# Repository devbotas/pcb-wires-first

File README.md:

# The Problem

Wireless IoT sucks.

It's unreliable and breaks all the time. There's not such thing as reliable, maintenance-free, wireless IoT.

If it runs on batteries - that's even worse.

Another problem - central IoT hubs. If those break, lose connection, decides to reboot ar whatever - my smart house immediatelly becomes non-functional.

# The Solution

Put the analog wires first! So that light switches continue to operate even if smart features decide to stop working.

# The Boards

## Gateway

This is a simple carrier board for WizNET W55RP20 development module. It cannot do much by itself - maybe blink some LEDs. Real functionality (and also power) should come from the JST PH headers.

Can be mounted on M or L size Holey board.

## Voltage converter

Takes 12-24V input (technically, 5-70V, but these voltages may not be supported on the other modules that this one is supposed to power) and creates 3.3V output so Gateway or other low power modules could be connected through the JST XH connector. Additionally, there are multiple JST VH connectors, which act as a power switch to connect multiple power hungry modules, like the Switcher.

Two can be mounted on a single Holey-S board.

## Switcher

Originally meant to control LED lights, but it can switch anything. It has one switchable 12/24V output (should be able to handle 4A). Output can be controlled simultaneously in multiple ways:

* ON wire: shorting this to GND for 100ms will turn the switch on.
* OFF wire: shorting this to GND for 100ms will turn the switch off.
* TGL wire: shorting this to GND for 100ms will toggle the switch.
* I2C directly: software based commands that can turn switch on or off and read the current state.

The idea here that ON/OFF/TGL signals could be wired to the physical wall switches directly, any smart features being entirely optional. So the switch will operate as a dumb-switch.

Renesas HVPAK SLG47115 chip serves both as a high-power switch and an input sanitizer. For example, if faulty hardware shorts ON signal to GND permanently, OFF and TGL signals continue to operate normally. 

Two can be mounted on a single Holey-S board.

## Holey boards

These are very handy to mount modules listed above, or maybe anything. They have a grid of 3.2mm diameter holes (hence the name) on a 5mm grid. They work perfectly with any M3 mounting hardware and come in the following sizes:

* L - 160x100 mm
* M - 100x80 mm
* S - 80x40 mm

So, one M board can fit exactly two S boards, and one L board can fit exactly 2 M boards. This allows some neat and functional arrangement.

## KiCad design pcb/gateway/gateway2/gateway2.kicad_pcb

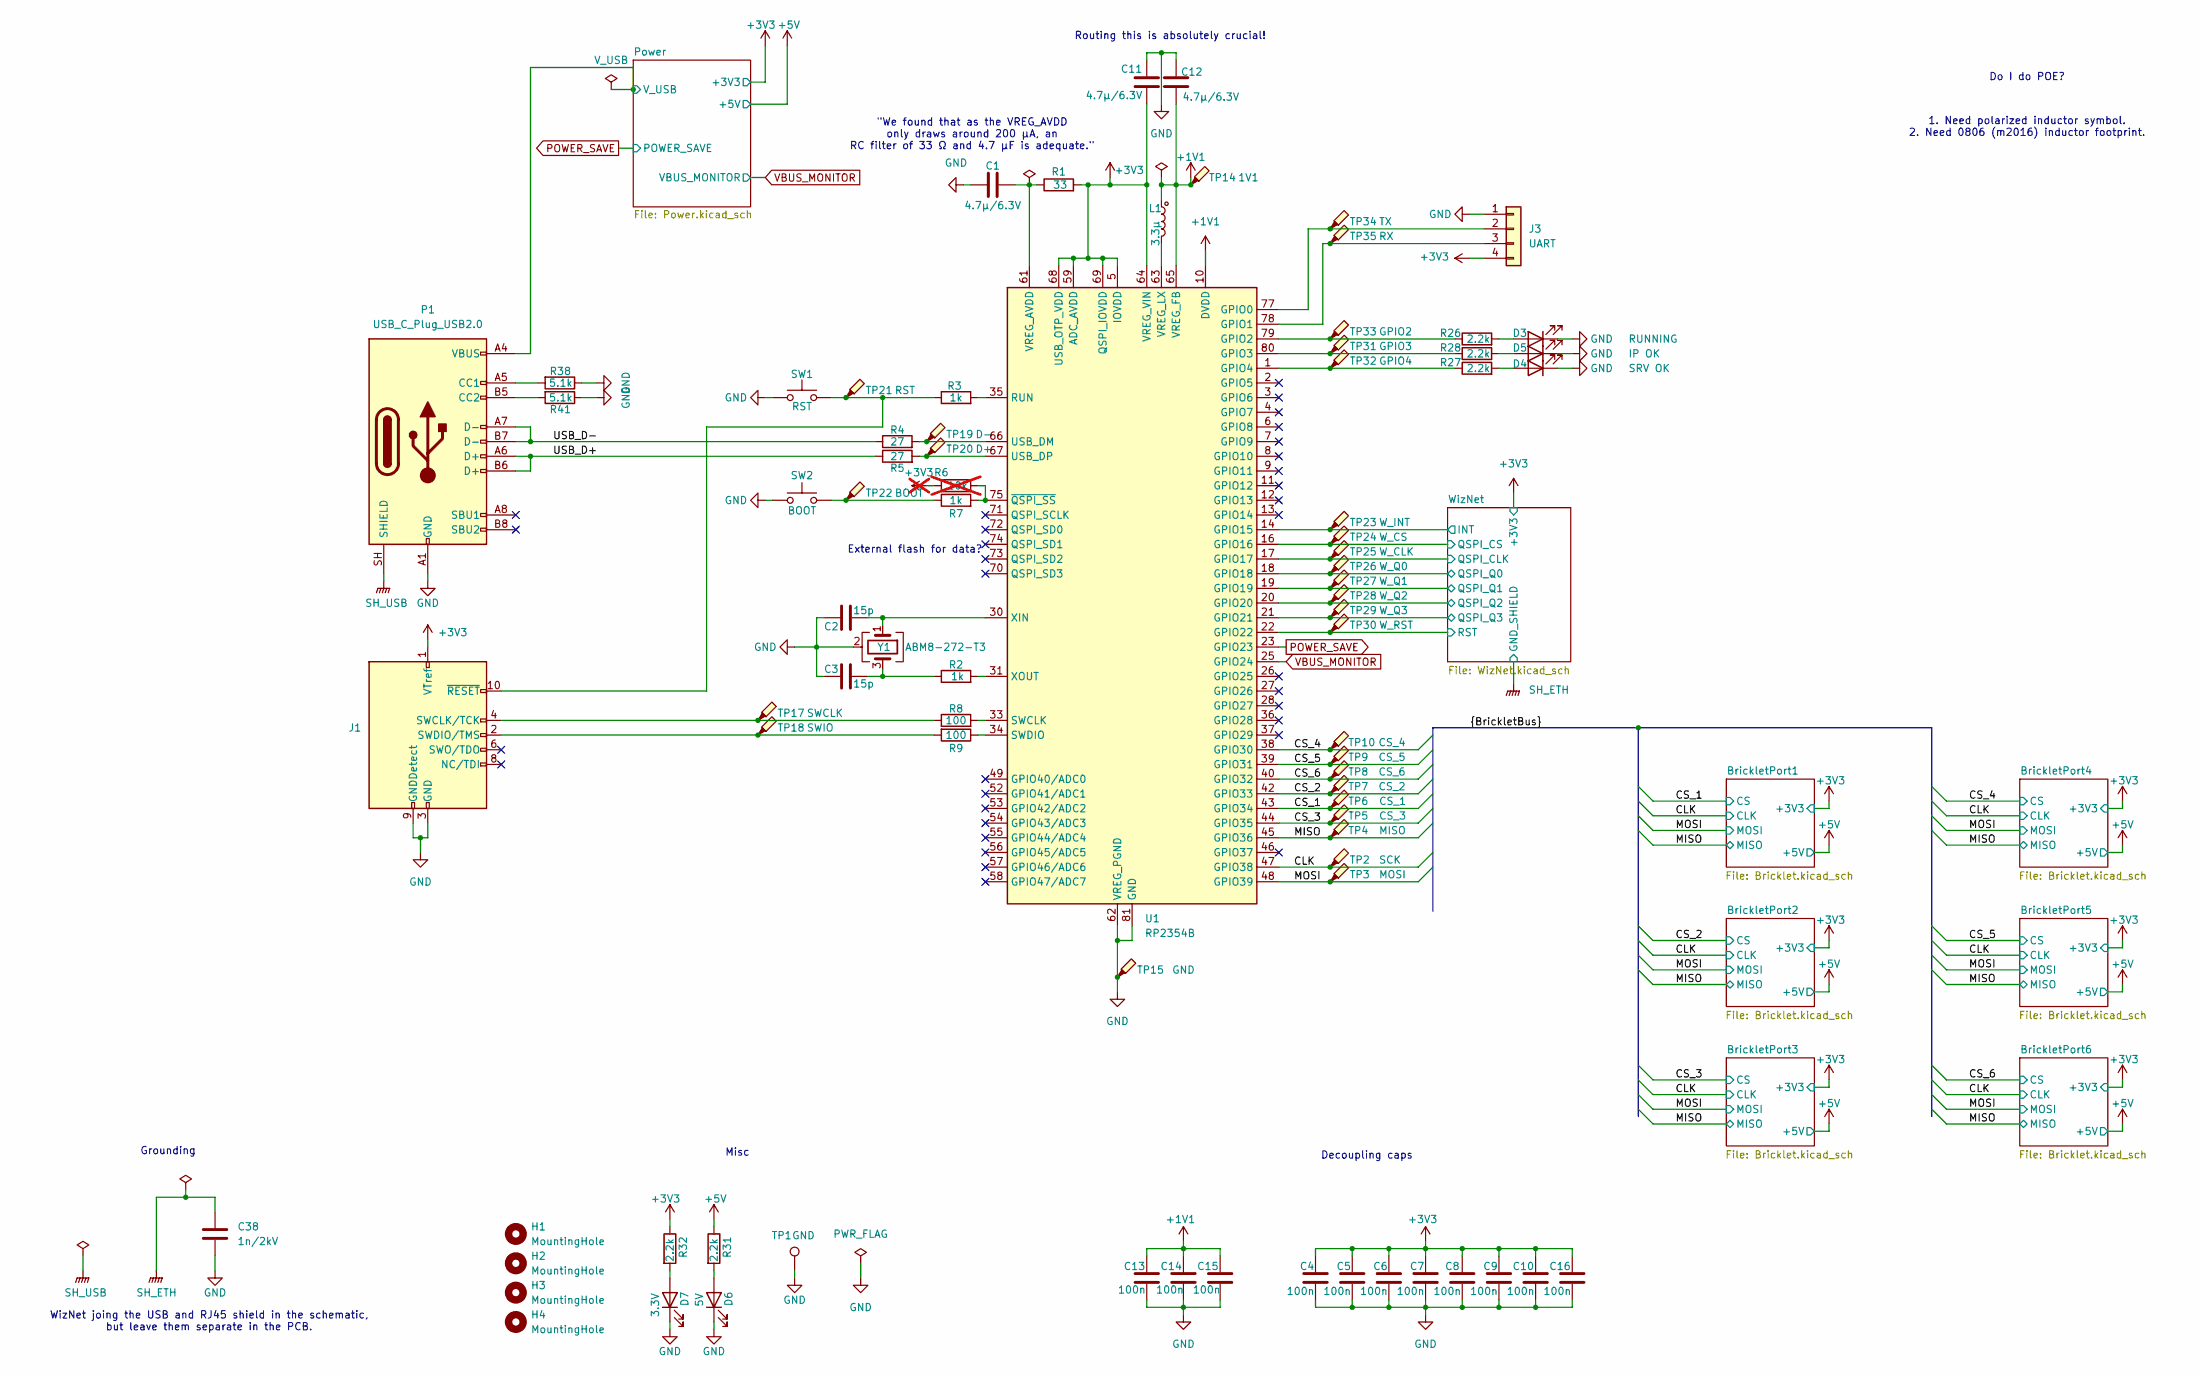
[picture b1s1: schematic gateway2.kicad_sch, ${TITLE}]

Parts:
C1, C11, C12: 4.7μ/6.3V; C_0603_1608Metric
C2, C3: 15p; C_0603_1608Metric
C4, C5, C6, C7, C8, C9, C10, C13, C14, C15, C16: 100n; C_0603_1608Metric
C38: 1n/2kV; C_0603_1608Metric
D3: RUNNING; D_0603_1608Metric
D4: SRV OK; D_0603_1608Metric
D5: IP OK; D_0603_1608Metric
D6: 5V; D_0603_1608Metric
D7: 3.3V; D_0603_1608Metric
H1, H2, H3, H4: MountingHole; MountingHole_3.2mm_M3_NoCopper
J1: Conn_ARM_JTAG_SWD_10; PinHeader_2x05_P1.27mm_Vertical_SMD
J3: UART; JST_PH_B4B-PH-K_1x04_P2.00mm_Vertical
L1: 3.3µ; L_Abracon_AOTA-B201610S
P1: USB_C_Plug_USB2.0; USB_C_Receptacle_GCT_USB4085
R1: 33; R_0603_1608Metric
R2, R3, R7: 1k; R_0603_1608Metric
R4, R5: 27; R_0603_1608Metric
R6: 10k; R_0603_1608Metric; not fitted
R8, R9: 100; R_0603_1608Metric
R26, R27, R28, R31, R32: 2.2k; R_0603_1608Metric
R38, R41: 5.1k; R_0603_1608Metric
SW1: RST; SW_SPST_CK_PTS815_Sx250SMTR_LFS
SW2: BOOT; SW_SPST_CK_PTS815_Sx250SMTR_LFS
TP1: GND; TestPoint_Keystone_5019_Miniature
TP2: SCK; TestPoint_Pad_D1.0mm
TP3: MOSI; TestPoint_Pad_D1.0mm
TP4: MISO; TestPoint_Pad_D1.0mm
TP5: CS_3; TestPoint_Pad_D1.0mm
TP6: CS_1; TestPoint_Pad_D1.0mm
TP7: CS_2; TestPoint_Pad_D1.0mm
TP8: CS_6; TestPoint_Pad_D1.0mm
TP9: CS_5; TestPoint_Pad_D1.0mm
TP10: CS_4; TestPoint_Pad_D1.0mm
TP14: 1V1; TestPoint_Pad_D1.0mm
TP15: GND; TestPoint_Pad_D1.0mm
TP17: SWCLK; TestPoint_Pad_D1.0mm
TP18: SWIO; TestPoint_Pad_D1.0mm
TP19: D-; TestPoint_Pad_D1.0mm
TP20: D+; TestPoint_Pad_D1.0mm
TP21: RST; TestPoint_Pad_D1.0mm
TP22: BOOT; TestPoint_Pad_D1.0mm
TP23: W_INT; TestPoint_Pad_D1.0mm
TP24: W_CS; TestPoint_Pad_D1.0mm
TP25: W_CLK; TestPoint_Pad_D1.0mm
TP26: W_Q0; TestPoint_Pad_D1.0mm
TP27: W_Q1; TestPoint_Pad_D1.0mm
TP28: W_Q2; TestPoint_Pad_D1.0mm
TP29: W_Q3; TestPoint_Pad_D1.0mm
TP30: W_RST; TestPoint_Pad_D1.0mm
TP31: GPIO3; TestPoint_Pad_D1.0mm
TP32: GPIO4; TestPoint_Pad_D1.0mm
TP33: GPIO2; TestPoint_Pad_D1.0mm
TP34: TX; TestPoint_Pad_D1.0mm
TP35: RX; TestPoint_Pad_D1.0mm
U1: RP2354B; QFN-80-1EP_10x10mm_P0.4mm_EP3.4x3.4mm
Y1: ABM8-272-T3; Crystal_SMD_Abracon_ABM8G-4Pin_3.2x2.5mm

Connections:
+1V1: C12.1, C13.2, C14.2, C15.2, L1.1, TP14.1 (1_1), U1.10 (DVDD), U1.32 (DVDD), U1.51 (DVDD), U1.65 (VREG_FB)
+3V3: C4.2, C5.2, C6.2, C7.2, C8.2, C9.2, C10.2, C11.1, C16.2, J1.1 (VTref), J3.4, R1.2, R6.1, R32.1, U1.5 (IOVDD), U1.15 (IOVDD), U1.24 (IOVDD), U1.29 (IOVDD), U1.41 (IOVDD), U1.50 (IOVDD), U1.59 (ADC_AVDD), U1.60 (IOVDD), U1.64 (VREG_VIN), U1.68 (USB_OTP_VDD), U1.69 (QSPI_IOVDD), U1.76 (IOVDD); also elsewhere on the board
+5V: R31.1; also elsewhere on the board
/CLK: TP2.1 (1_1), U1.47 (GPIO38); also elsewhere on the board
/CS_1: TP6.1 (1_1), U1.43 (GPIO34); also elsewhere on the board
/CS_2: TP7.1 (1_1), U1.42 (GPIO33); also elsewhere on the board
/CS_3: TP5.1 (1_1), U1.44 (GPIO35); also elsewhere on the board
/CS_4: TP10.1 (1_1), U1.38 (GPIO30); also elsewhere on the board
/CS_5: TP9.1 (1_1), U1.39 (GPIO31); also elsewhere on the board
/CS_6: TP8.1 (1_1), U1.40 (GPIO32); also elsewhere on the board
/MISO: TP4.1 (1_1), U1.45 (GPIO36); also elsewhere on the board
/MOSI: TP3.1 (1_1), U1.48 (GPIO39); also elsewhere on the board
/Power/V_USB: P1.A4 (VBUS), P1.A9 (VBUS), P1.B4 (VBUS), P1.B9 (VBUS); also elsewhere on the board
/USB_D+: P1.A6 (D+), P1.B6 (D+), R5.1
/USB_D-: P1.A7 (D-), P1.B7 (D-), R4.1
/WizNet/INT: TP23.1 (1_1), U1.14 (GPIO15); also elsewhere on the board
/WizNet/QSPI_CLK: TP25.1 (1_1), U1.17 (GPIO17); also elsewhere on the board
/WizNet/QSPI_CS: TP24.1 (1_1), U1.16 (GPIO16); also elsewhere on the board
/WizNet/QSPI_Q0: TP26.1 (1_1), U1.18 (GPIO18); also elsewhere on the board
/WizNet/QSPI_Q1: TP27.1 (1_1), U1.19 (GPIO19); also elsewhere on the board
/WizNet/QSPI_Q2: TP28.1 (1_1), U1.20 (GPIO20); also elsewhere on the board
/WizNet/QSPI_Q3: TP29.1 (1_1), U1.21 (GPIO21); also elsewhere on the board
/WizNet/RST: TP30.1 (1_1), U1.22 (GPIO22); also elsewhere on the board
GND: C1.1, C2.1, C3.1, C4.1, C5.1, C6.1, C7.1, C8.1, C9.1, C10.1, C11.2, C12.2, C13.1, C14.1, C15.1, C16.1, C38.1, D3.1 (K), D4.1 (K), D5.1 (K), D6.1 (K), D7.1 (K), J1.3 (GND), J1.5 (GND), J1.9 (GNDDetect), J3.1, P1.A1 (GND), P1.A12 (GND), P1.B1 (GND), P1.B12 (GND), R38.1, R41.1, SW1.1, SW2.1, TP1.1 (1_1), TP15.1 (1_1), U1.62 (VREG_PGND), U1.81 (GND), Y1.2 (G), Y1.4 (G); also elsewhere on the board
unnamed: C3.2, R2.1, Y1.3
unnamed: D3.2 (A), R26.2
unnamed: D4.2 (A), R27.2
unnamed: D5.2 (A), R28.2
unnamed: D6.2 (A), R31.2
unnamed: D7.2 (A), R32.2
unnamed: J1.4 (SWCLK/TCK), R8.1, TP17.1 (1_1)
unnamed: J1.2 (SWDIO/TMS), R9.2, TP18.1 (1_1)
unnamed: J1.10 (~RESET), R3.1, SW1.2, TP21.1 (1_1)
unnamed: J3.2, TP34.1 (1_1), U1.77 (GPIO0)
unnamed: J3.3, TP35.1 (1_1), U1.78 (GPIO1)
unnamed: P1.A5 (CC1), R38.2
unnamed: P1.B5 (CC2), R41.2
unnamed: R7.1, SW2.2, TP22.1 (1_1)
unnamed: R26.1, TP33.1 (1_1), U1.79 (GPIO2)
unnamed: R28.1, TP31.1 (1_1), U1.80 (GPIO3)
unnamed: R27.1, TP32.1 (1_1), U1.1 (GPIO4)
unnamed: R3.2, U1.35 (RUN)
unnamed: R8.2, U1.33 (SWCLK)
unnamed: R9.1, U1.34 (SWDIO)
unnamed: R4.2, TP19.1 (1_1), U1.66 (USB_DM)
unnamed: R5.2, TP20.1 (1_1), U1.67 (USB_DP)
unnamed: C1.2, R1.1, U1.61 (VREG_AVDD)
unnamed: L1.2, U1.63 (VREG_LX)
unnamed: C2.2, U1.30 (XIN), Y1.1
unnamed: R2.2, U1.31 (XOUT)
unnamed: R6.2, R7.2, U1.75 (~QSPI_SS)
POWER_SAVE: U1.23 (GPIO23); also elsewhere on the board
SH_ETH: C38.2; also elsewhere on the board
SH_USB: P1.SH (SHIELD)
VBUS_MONITOR: U1.25 (GPIO24); also elsewhere on the board

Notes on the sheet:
Decoupling caps
Routing this is absolutely crucial!
1. Need polarized inductor symbol. 2. Need 0806 (m2016) inductor footprint.
WizNet joing the USB and RJ45 shield in the schematic, but leave them separate in the PCB.
Grounding
External flash for data?
Do I do POE?
Misc
"We found that as the VREG_AVDD only draws around 200 μA, an RC filter of 33 Ω and 4.7 μF is adequate."

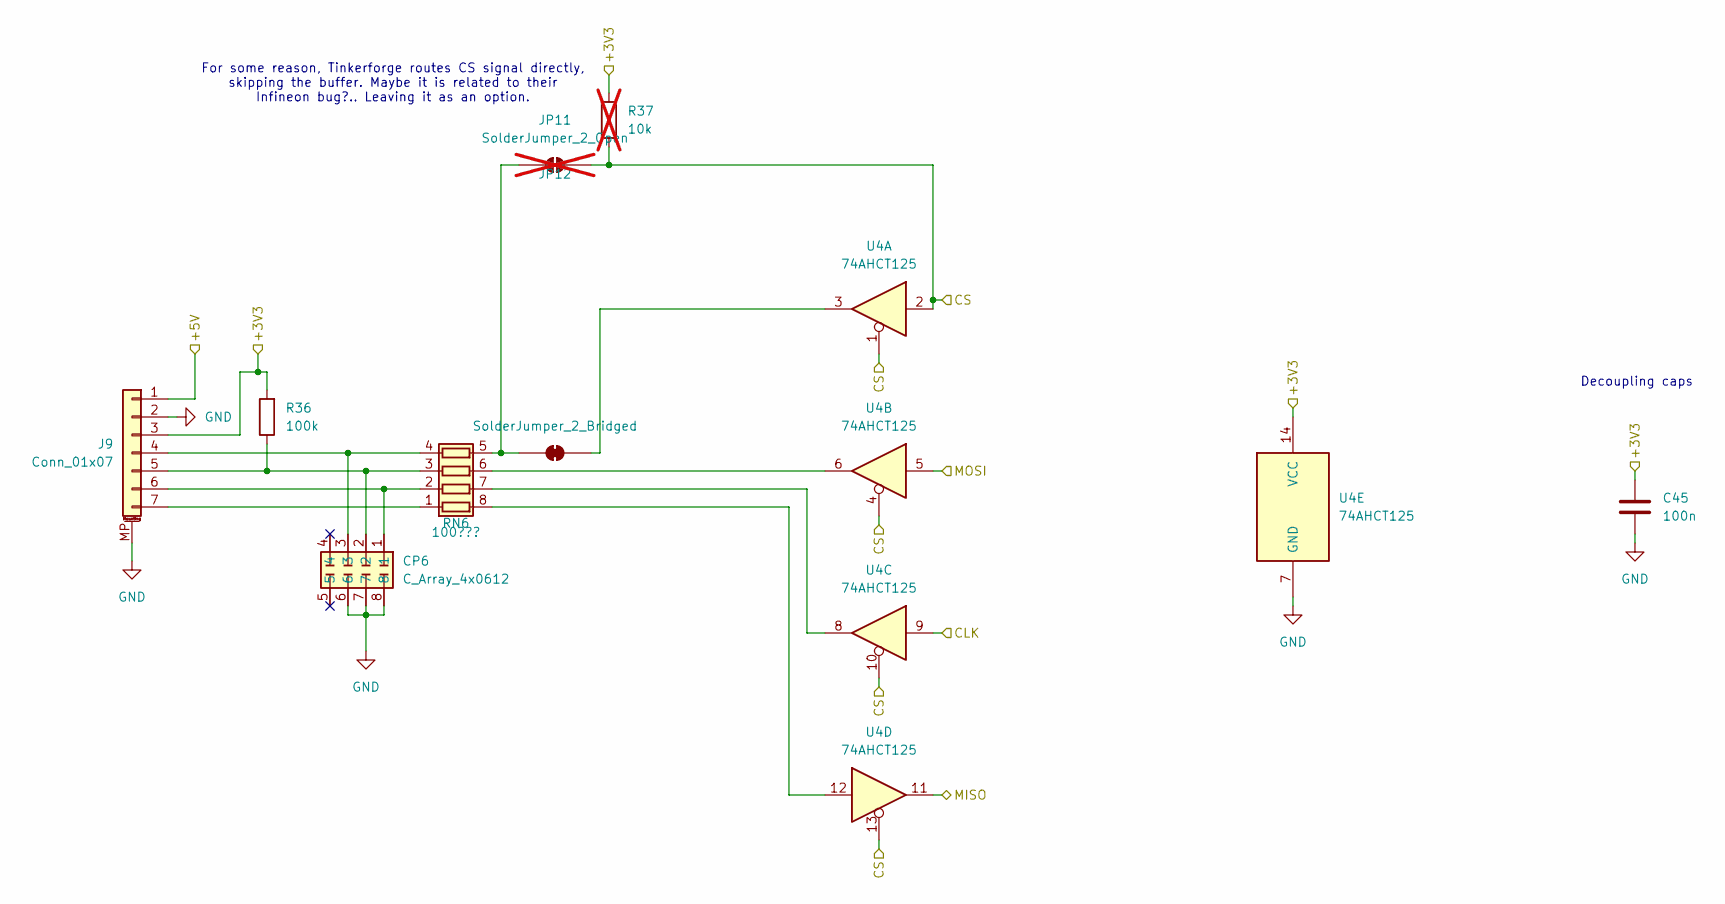
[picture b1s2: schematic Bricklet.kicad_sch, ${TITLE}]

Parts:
C45: 100n; C_0603_1608Metric
CP6: C_Array_4x0612
J9: Conn_01x07; JST_GH_BM07B-GHS-TBT_1x07-1MP_P1.25mm_Vertical
JP11: SolderJumper_2_Open; SolderJumper-2_P1.3mm_Open_RoundedPad1.0x1.5mm; not fitted
JP12: SolderJumper_2_Bridged; SolderJumper-2_P1.3mm_Bridged_RoundedPad1.0x1.5mm
R36: 100k; R_0603_1608Metric
R37: 10k; R_0603_1608Metric; not fitted
RN6: 100???; R_Array_Concave_4x0603
U4: 74AHCT125; DHVQFN-14-1EP_2.5x3mm_P0.5mm_EP1x1.5mm

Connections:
+3V3: C45.2, J9.3, R36.2, R37.2, U4.14 (VCC); also elsewhere on the board
+5V: J9.1; also elsewhere on the board
/CLK: U4.9; also elsewhere on the board
/CS_1: JP11.1 (A), R37.1, U4.1, U4.2, U4.4, U4.10, U4.13; also elsewhere on the board
/MISO: U4.11; also elsewhere on the board
/MOSI: U4.5; also elsewhere on the board
GND: C45.1, CP6.6, CP6.7, CP6.8, J9.2, J9.MP (MountPin), U4.7 (GND); also elsewhere on the board
unnamed: CP6.3, J9.4, RN6.4 (R4.1)
unnamed: CP6.2, J9.5, R36.1, RN6.3 (R3.1)
unnamed: CP6.1, J9.6, RN6.2 (R2.1)
unnamed: J9.7, RN6.1 (R1.1)
unnamed: JP11.2 (B), JP12.1 (A), RN6.5 (R4.2)
unnamed: JP12.2 (B), U4.3
unnamed: RN6.8 (R1.2), U4.12
unnamed: RN6.7 (R2.2), U4.8
unnamed: RN6.6 (R3.2), U4.6

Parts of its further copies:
C42, C46, C47, C48, C49: 100n; C_0603_1608Metric
CP5, CP7, CP8, CP9, CP10: C_Array_4x0612
J8, J10, J11, J12, J13: Conn_01x07; JST_GH_BM07B-GHS-TBT_1x07-1MP_P1.25mm_Vertical
JP9, JP13, JP15, JP17, JP19: SolderJumper_2_Open; SolderJumper-2_P1.3mm_Open_RoundedPad1.0x1.5mm; not fitted
JP10, JP14, JP16, JP18, JP20: SolderJumper_2_Bridged; SolderJumper-2_P1.3mm_Bridged_RoundedPad1.0x1.5mm
R34, R39, R42, R44, R46: 100k; R_0603_1608Metric
R35, R40, R43, R45, R47: 10k; R_0603_1608Metric; not fitted
U5, U6, U7, U14, U15: 74AHCT125; DHVQFN-14-1EP_2.5x3mm_P0.5mm_EP1x1.5mm

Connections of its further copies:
+3V3: C42.2, C46.2, C47.2, C48.2, C49.2, J8.3, J10.3, J11.3, J12.3, J13.3, R34.2, R35.2, R39.2, R40.2, R42.2, R43.2, R44.2, R45.2, R46.2, R47.2, U5.14 (VCC), U6.14 (VCC), U7.14 (VCC), U14.14 (VCC), U15.14 (VCC); also elsewhere on the board
+5V: J8.1, J10.1, J11.1, J12.1, J13.1; also elsewhere on the board
/CLK: U5.9, U6.9, U7.9, U14.9, U15.9; also elsewhere on the board
/CS_2: JP9.1 (A), R35.1, U14.1, U14.2, U14.4, U14.10, U14.13; also elsewhere on the board
/CS_3: JP13.1 (A), R40.1, U5.1, U5.2, U5.4, U5.10, U5.13; also elsewhere on the board
/CS_4: JP15.1 (A), R43.1, U6.1, U6.2, U6.4, U6.10, U6.13; also elsewhere on the board
/CS_5: JP17.1 (A), R45.1, U7.1, U7.2, U7.4, U7.10, U7.13; also elsewhere on the board
/CS_6: JP19.1 (A), R47.1, U15.1, U15.2, U15.4, U15.10, U15.13; also elsewhere on the board
/MISO: U5.11, U6.11, U7.11, U14.11, U15.11; also elsewhere on the board
/MOSI: U5.5, U6.5, U7.5, U14.5, U15.5; also elsewhere on the board
GND: C42.1, C46.1, C47.1, C48.1, C49.1, CP5.6, CP5.7, CP5.8, CP7.6, CP7.7, CP7.8, CP8.6, CP8.7, CP8.8, CP9.6, CP9.7, CP9.8, CP10.6, CP10.7, CP10.8, J8.2, J8.MP (MountPin), J10.2, J10.MP (MountPin), J11.2, J11.MP (MountPin), J12.2, J12.MP (MountPin), J13.2, J13.MP (MountPin), U5.7 (GND), U6.7 (GND), U7.7 (GND), U14.7 (GND), U15.7 (GND); also elsewhere on the board
unnamed 48: CP5.3, J8.4; also elsewhere on the board
unnamed 49: CP5.2, J8.5, R34.1; also elsewhere on the board
unnamed 50: CP5.1, J8.6; also elsewhere on the board
unnamed 51: J8.7; also elsewhere on the board
unnamed 56: CP7.3, J10.4; also elsewhere on the board
unnamed 57: CP7.2, J10.5, R39.1; also elsewhere on the board
unnamed 58: CP7.1, J10.6; also elsewhere on the board
unnamed 59: J10.7; also elsewhere on the board
unnamed 60: CP8.3, J11.4; also elsewhere on the board
unnamed 61: CP8.2, J11.5, R42.1; also elsewhere on the board
unnamed 62: CP8.1, J11.6; also elsewhere on the board
unnamed 63: J11.7; also elsewhere on the board
unnamed 64: CP9.3, J12.4; also elsewhere on the board
unnamed 65: CP9.2, J12.5, R44.1; also elsewhere on the board
unnamed 66: CP9.1, J12.6; also elsewhere on the board
unnamed 67: J12.7; also elsewhere on the board
unnamed 68: CP10.3, J13.4; also elsewhere on the board
unnamed 69: CP10.2, J13.5, R46.1; also elsewhere on the board
unnamed 70: CP10.1, J13.6; also elsewhere on the board
unnamed 71: J13.7; also elsewhere on the board
unnamed 72: JP9.2 (B), JP10.1 (A); also elsewhere on the board
unnamed: JP10.2 (B), U14.3
unnamed 76: JP13.2 (B), JP14.1 (A); also elsewhere on the board
unnamed: JP14.2 (B), U5.3
unnamed 78: JP15.2 (B), JP16.1 (A); also elsewhere on the board
unnamed: JP16.2 (B), U6.3
unnamed 80: JP17.2 (B), JP18.1 (A); also elsewhere on the board
unnamed: JP18.2 (B), U7.3
unnamed 82: JP19.2 (B), JP20.1 (A); also elsewhere on the board
unnamed: JP20.2 (B), U15.3
unnamed 88: U14.12; also elsewhere on the board
unnamed 89: U14.8; also elsewhere on the board
unnamed 90: U14.6; also elsewhere on the board
unnamed 94: U5.12; also elsewhere on the board
unnamed 95: U5.8; also elsewhere on the board
unnamed 96: U5.6; also elsewhere on the board
unnamed 97: U6.12; also elsewhere on the board
unnamed 98: U6.8; also elsewhere on the board
unnamed 99: U6.6; also elsewhere on the board
unnamed 100: U7.12; also elsewhere on the board
unnamed 101: U7.8; also elsewhere on the board
unnamed 102: U7.6; also elsewhere on the board
unnamed 103: U15.12; also elsewhere on the board
unnamed 104: U15.8; also elsewhere on the board
unnamed 105: U15.6; also elsewhere on the board

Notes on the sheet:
For some reason, Tinkerforge routes CS signal directly, skipping the buffer. Maybe it is related to their Infineon bug?.. Leaving it as an option.
Decoupling caps

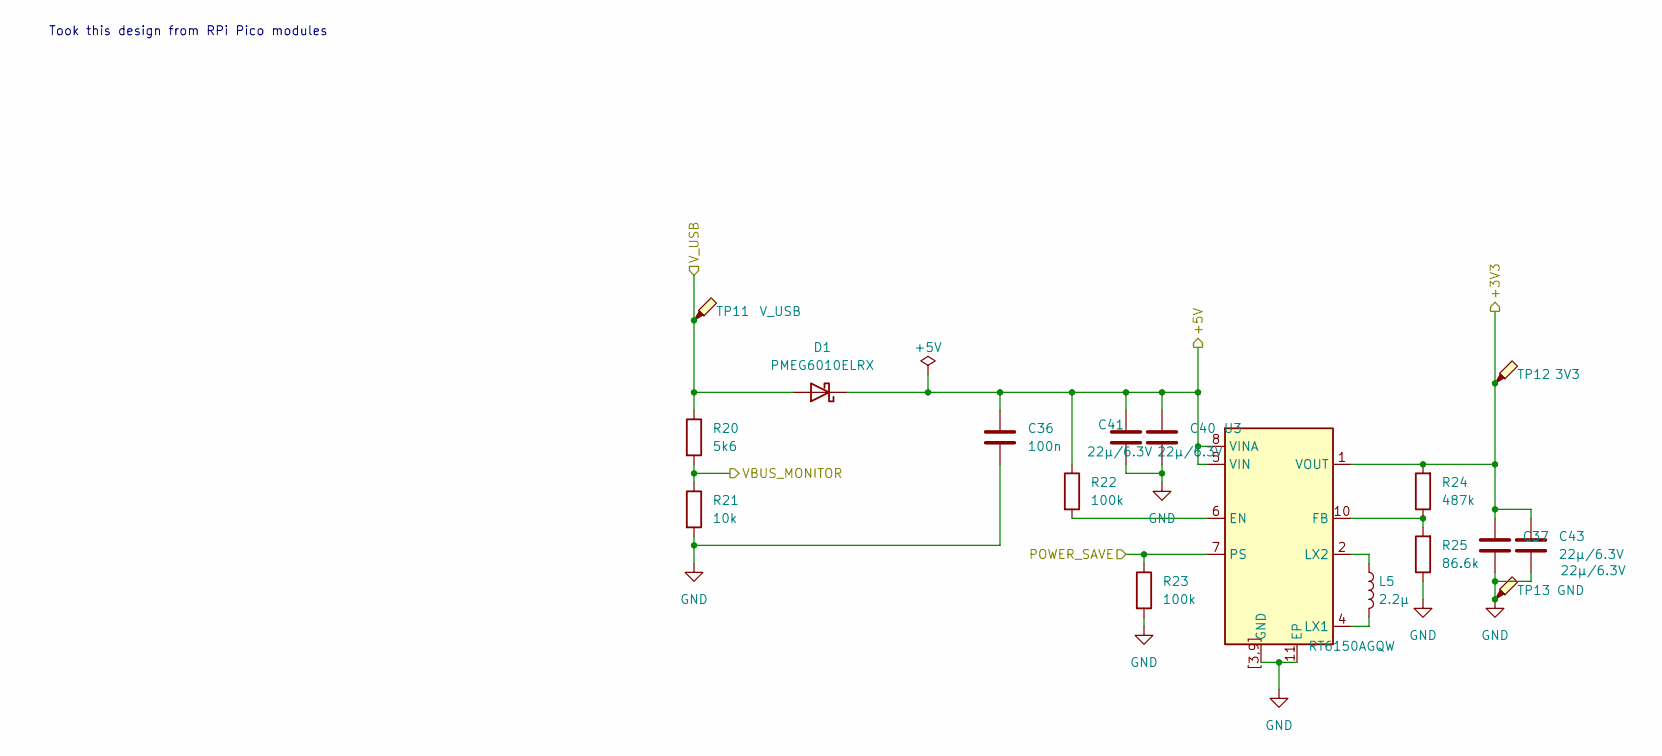
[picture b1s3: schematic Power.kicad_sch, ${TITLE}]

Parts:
C36: 100n; C_0603_1608Metric
C37, C40, C41, C43: 22μ/6.3V; C_1206_3216Metric
D1: PMEG6010ELRX; Nexperia_CFP3_SOD-123W
L5: 2.2μ; L_1206_3216Metric
R20: 5k6; R_0603_1608Metric
R21: 10k; R_0603_1608Metric
R22, R23: 100k; R_0603_1608Metric
R24: 487k; R_0603_1608Metric
R25: 86.6k; R_0603_1608Metric
TP11: V_USB; TestPoint_Pad_D1.0mm
TP12: 3V3; TestPoint_Pad_D1.0mm
TP13: GND; TestPoint_Pad_D1.0mm
U3: RT6150AGQW; WDFN-10-1EP_3x3mm_P0.5mm_EP1.8x2.5mm

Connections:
+3V3: C37.2, C43.2, R24.2, TP12.1 (1_1), U3.1 (VOUT); also elsewhere on the board
+5V: C36.2, C40.2, C41.2, D1.1 (K), R22.1, U3.5 (VIN), U3.8 (VINA); also elsewhere on the board
/Power/V_USB: D1.2 (A), R20.1, TP11.1 (1_1); also elsewhere on the board
GND: C36.1, C37.1, C40.1, C41.1, C43.1, R21.2, R23.2, R25.1, TP13.1 (1_1), U3.3 (GND), U3.9 (GND), U3.11 (EP), U3.[3,9] (GND); also elsewhere on the board
unnamed: R22.2, U3.6 (EN)
unnamed: R24.1, R25.2, U3.10 (FB)
unnamed: L5.2, U3.4 (LX1)
unnamed: L5.1, U3.2 (LX2)
POWER_SAVE: R23.1, U3.7 (PS); also elsewhere on the board
VBUS_MONITOR: R20.2, R21.1; also elsewhere on the board

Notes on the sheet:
Took this design from RPi Pico modules

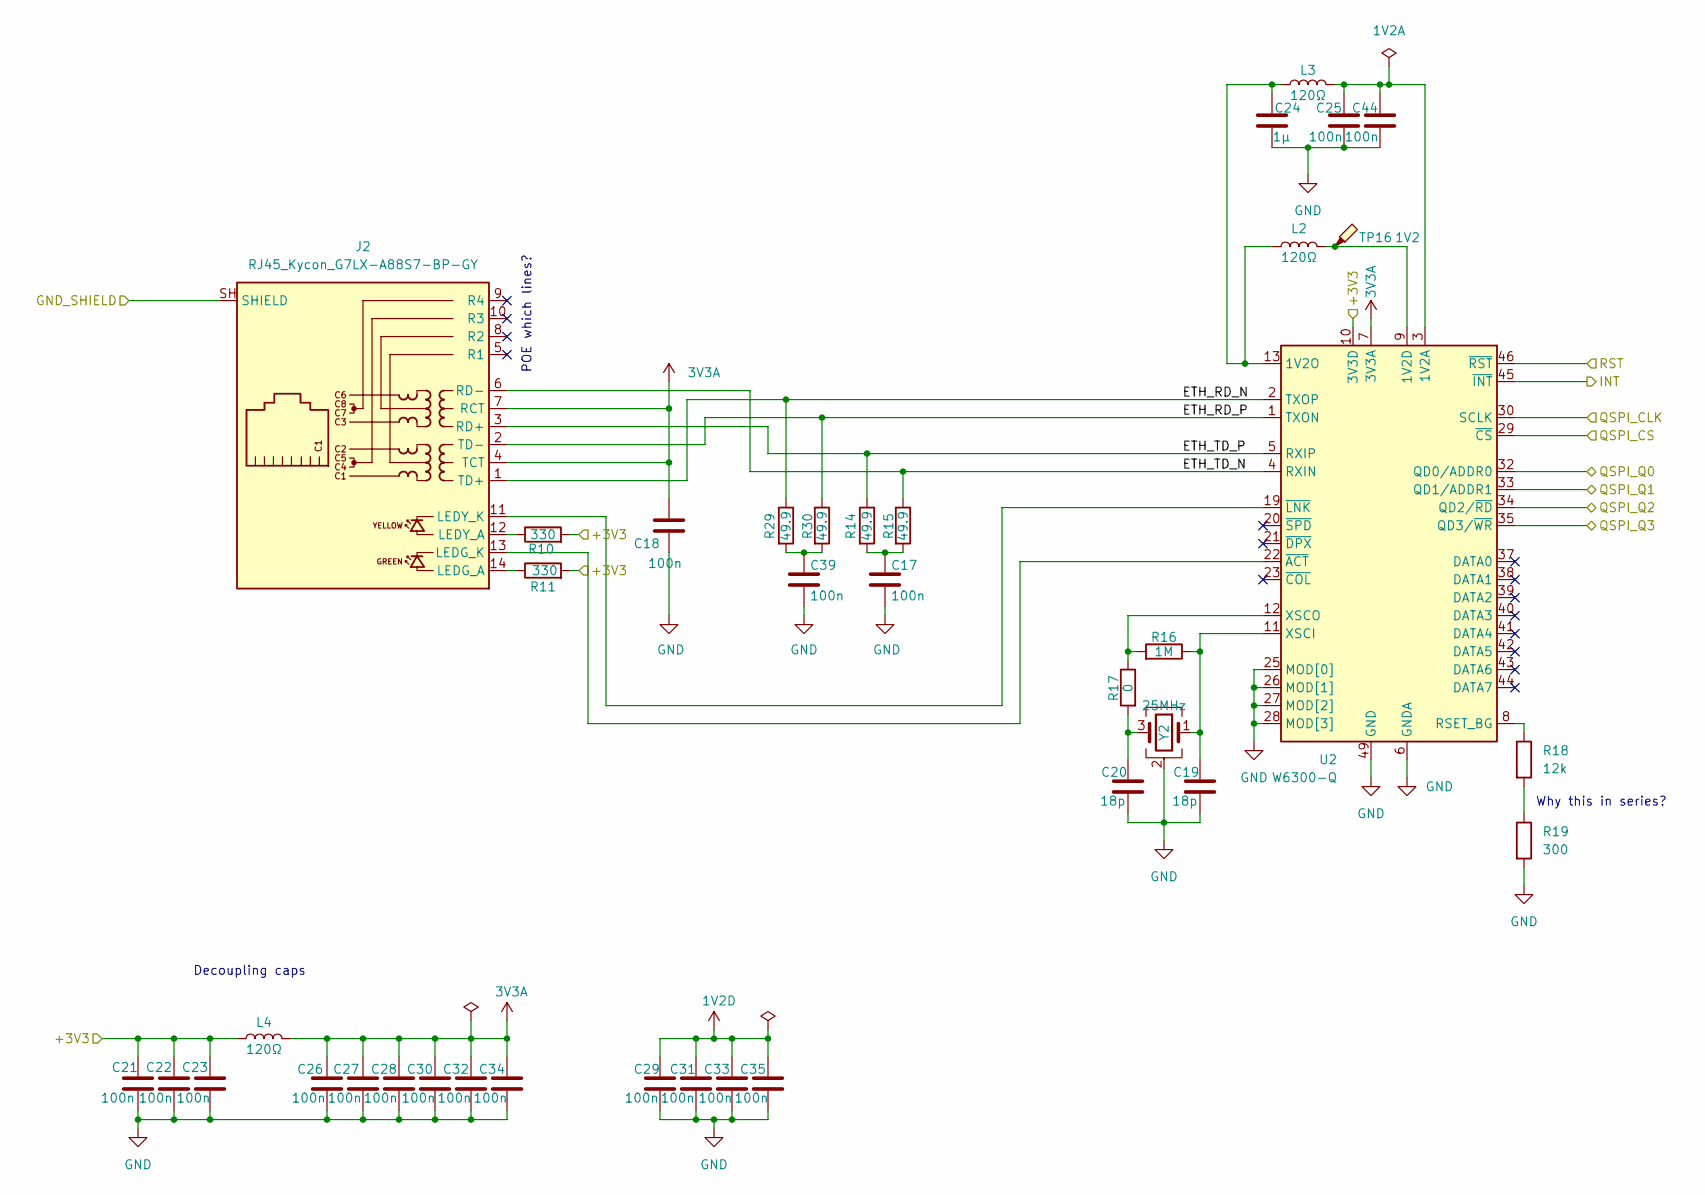
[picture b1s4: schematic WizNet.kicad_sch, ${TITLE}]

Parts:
C17, C18, C21, C22, C23, C25, C26, C27, C28, C29, C30, C31, C32, C33, C34, C35, C39, C44: 100n; C_0603_1608Metric
C19, C20: 18p; C_0603_1608Metric
C24: 1µ; C_0603_1608Metric
J2: RJ45_Kycon_G7LX-A88S7-BP-GY; RJ45_Kycon_G7LX-A88S7-BP-xx_Horizontal
L2, L3, L4: 120Ω; L_0603_1608Metric; MPN MPZ1608S121ATDH5
R10, R11: 330; R_0603_1608Metric
R14, R15, R29, R30: 49.9; R_0603_1608Metric
R16: 1M; R_0603_1608Metric
R17: 0; R_0603_1608Metric
R18: 12k; R_0603_1608Metric
R19: 300; R_0603_1608Metric
TP16: 1V2; TestPoint_Pad_D1.0mm
U2: W6300-Q; LQFP-48-1EP_7x7mm_P0.5mm_EP3.6x3.6mm
Y2: 25MHz; Crystal_SMD_Abracon_ABM8G-4Pin_3.2x2.5mm

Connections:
1V2A: C25.2, C44.2, L3.2, U2.3 (1V2A), U2.16 (1V2A)
3V3A: C18.2, C26.2, C27.2, C28.2, C30.2, C32.2, C34.2, J2.4 (TCT), J2.7 (RCT), L4.2, U2.7 (3V3A), U2.14 (3V3A)
+3V3: C21.2, C22.2, C23.2, L4.1, R10.2, R11.2, U2.10 (3V3D), U2.24 (3V3D), U2.36 (3V3D); also elsewhere on the board
/WizNet/ETH_RD_N: J2.1 (TD+), R29.1, U2.2 (TXOP)
/WizNet/ETH_RD_P: J2.2 (TD-), R30.1, U2.1 (TXON)
/WizNet/ETH_TD_N: J2.6 (RD-), R15.1, U2.4 (RXIN)
/WizNet/ETH_TD_P: J2.3 (RD+), R14.1, U2.5 (RXIP)
/WizNet/INT: U2.45 (~INT); also elsewhere on the board
/WizNet/QSPI_CLK: U2.30 (SCLK); also elsewhere on the board
/WizNet/QSPI_CS: U2.29 (~CS); also elsewhere on the board
/WizNet/QSPI_Q0: U2.32 (QD0/ADDR0); also elsewhere on the board
/WizNet/QSPI_Q1: U2.33 (QD1/ADDR1); also elsewhere on the board
/WizNet/QSPI_Q2: U2.34 (QD2/~RD); also elsewhere on the board
/WizNet/QSPI_Q3: U2.35 (QD3/~WR); also elsewhere on the board
/WizNet/RST: U2.46 (~RST); also elsewhere on the board
GND: C17.1, C18.1, C19.1, C20.1, C21.1, C22.1, C23.1, C24.1, C25.1, C26.1, C27.1, C28.1, C29.1, C30.1, C31.1, C32.1, C33.1, C34.1, C35.1, C39.1, C44.1, R19.2, U2.6 (GNDA), U2.15 (GNDA), U2.17 (GNDA), U2.25 (MOD[0]), U2.26 (MOD[1]), U2.27 (MOD[2]), U2.28 (MOD[3]), U2.48 (GNDA), U2.49 (GND), Y2.2 (G), Y2.4 (G); also elsewhere on the board
unnamed: C17.2, R14.2, R15.2
unnamed: C20.2, R17.2, Y2.3
unnamed: C39.2, R29.2, R30.2
unnamed: J2.14 (LEDG_A), R11.1
unnamed: J2.13 (LEDG_K), U2.22 (~ACT)
unnamed: J2.12 (LEDY_A), R10.1
unnamed: J2.11 (LEDY_K), U2.19 (~LNK)
unnamed: R18.2, R19.1
unnamed: C24.2, L2.1, L3.1, U2.13 (1V2O)
unnamed: R18.1, U2.8 (RSET_BG)
unnamed: C19.2, R16.1, U2.11 (XSCI), Y2.1
unnamed: R16.2, R17.1, U2.12 (XSCO)
SH_ETH: J2.SH (SHIELD); also elsewhere on the board

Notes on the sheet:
Decoupling caps
POE which lines?
Why this in series?

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
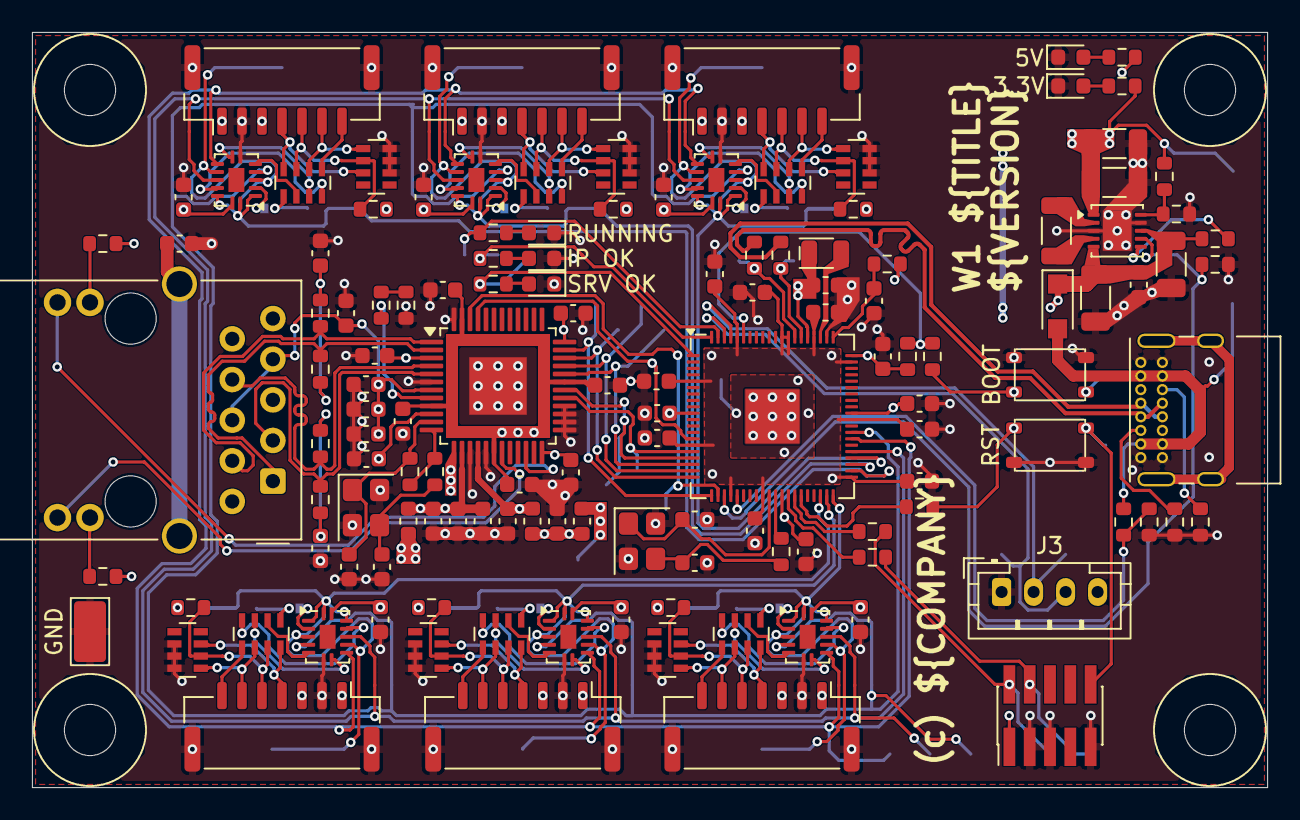
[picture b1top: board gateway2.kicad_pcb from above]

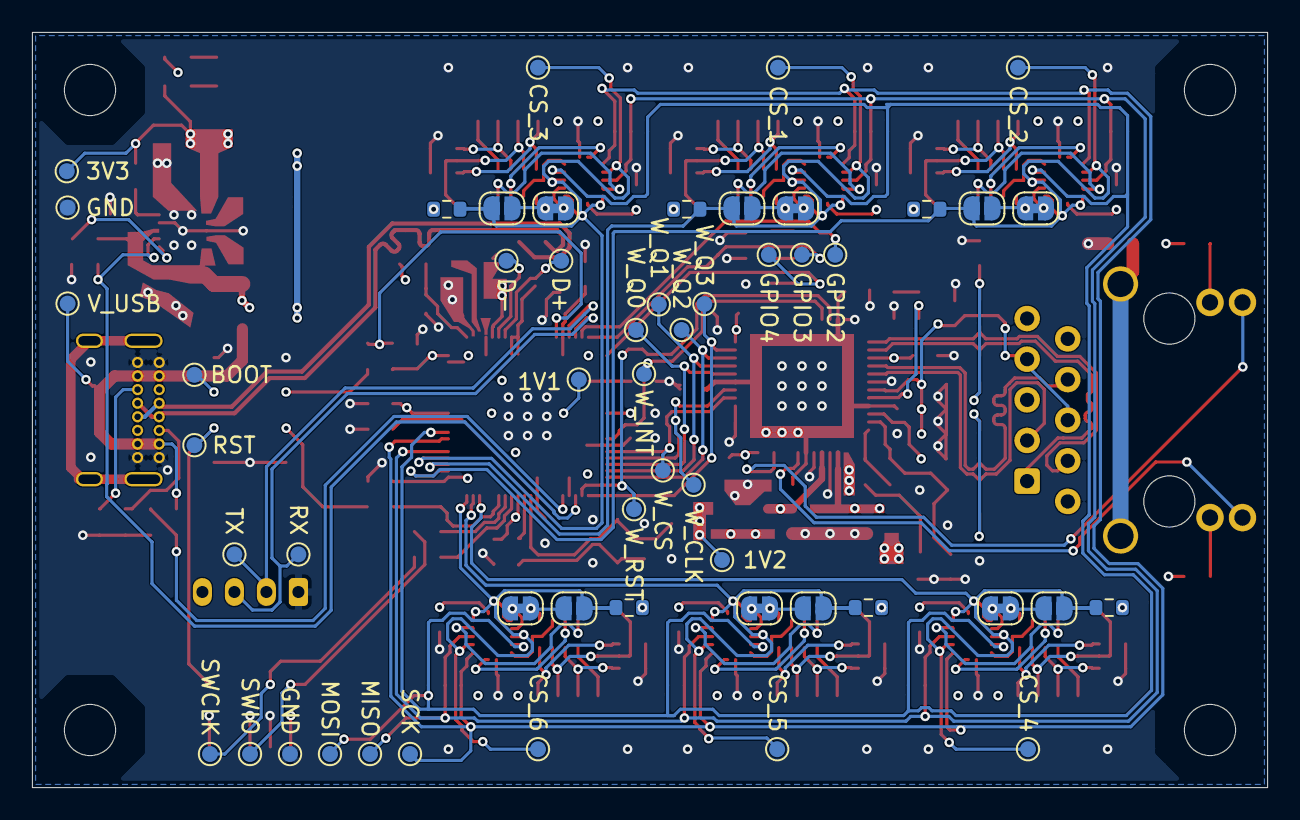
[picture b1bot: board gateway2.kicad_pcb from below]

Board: 4 copper layers, 77.2 x 47.2 mm, 190 parts (52 on the bottom side), 131 nets.

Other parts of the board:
RN5, RN7, RN8, RN9, RN10: R_Pack04; R_Array_Concave_4x0603

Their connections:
unnamed 48: RN5.4 (R4.1); also elsewhere on the board
unnamed 49: RN5.3 (R3.1); also elsewhere on the board
unnamed 50: RN5.2 (R2.1); also elsewhere on the board
unnamed 51: RN5.1 (R1.1); also elsewhere on the board
unnamed 56: RN7.4 (R4.1); also elsewhere on the board
unnamed 57: RN7.3 (R3.1); also elsewhere on the board
unnamed 58: RN7.2 (R2.1); also elsewhere on the board
unnamed 59: RN7.1 (R1.1); also elsewhere on the board
unnamed 60: RN8.4 (R4.1); also elsewhere on the board
unnamed 61: RN8.3 (R3.1); also elsewhere on the board
unnamed 62: RN8.2 (R2.1); also elsewhere on the board
unnamed 63: RN8.1 (R1.1); also elsewhere on the board
unnamed 64: RN9.4 (R4.1); also elsewhere on the board
unnamed 65: RN9.3 (R3.1); also elsewhere on the board
unnamed 66: RN9.2 (R2.1); also elsewhere on the board
unnamed 67: RN9.1 (R1.1); also elsewhere on the board
unnamed 68: RN10.4 (R4.1); also elsewhere on the board
unnamed 69: RN10.3 (R3.1); also elsewhere on the board
unnamed 70: RN10.2 (R2.1); also elsewhere on the board
unnamed 71: RN10.1 (R1.1); also elsewhere on the board
unnamed 72: RN5.5 (R4.2); also elsewhere on the board
unnamed 76: RN7.5 (R4.2); also elsewhere on the board
unnamed 78: RN8.5 (R4.2); also elsewhere on the board
unnamed 80: RN9.5 (R4.2); also elsewhere on the board
unnamed 82: RN10.5 (R4.2); also elsewhere on the board
unnamed 88: RN5.8 (R1.2); also elsewhere on the board
unnamed 89: RN5.7 (R2.2); also elsewhere on the board
unnamed 90: RN5.6 (R3.2); also elsewhere on the board
unnamed 94: RN7.8 (R1.2); also elsewhere on the board
unnamed 95: RN7.7 (R2.2); also elsewhere on the board
unnamed 96: RN7.6 (R3.2); also elsewhere on the board
unnamed 97: RN8.8 (R1.2); also elsewhere on the board
unnamed 98: RN8.7 (R2.2); also elsewhere on the board
unnamed 99: RN8.6 (R3.2); also elsewhere on the board
unnamed 100: RN9.8 (R1.2); also elsewhere on the board
unnamed 101: RN9.7 (R2.2); also elsewhere on the board
unnamed 102: RN9.6 (R3.2); also elsewhere on the board
unnamed 103: RN10.8 (R1.2); also elsewhere on the board
unnamed 104: RN10.7 (R2.2); also elsewhere on the board
unnamed 105: RN10.6 (R3.2); also elsewhere on the board

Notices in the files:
pcb/pcb-wires-first.kicad_pcb:
Copyright (c) devbotas
